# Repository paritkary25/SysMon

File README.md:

# SysMon
SysMon is a system monitor hardware. It has three parts
- USB hub
- macro keys and a volume knob as an input (knobs are cool)
- three strips of multiple colours showing CPU/GPU/RAM usage
The project is ongoing.

.
├── CAD: Contains all the CADs related to the project
├── PCB: Contains the PCB files
├── Software: Software used in this project
└── USB-C_dim_xtracn: An overkill exercise to obtain the correct placement of the holes of the USB-C module

## Progress
- CAD: Complete and printed
- PCB: Complete and printed
    - The USB hub is working
    - STM32 is yet to be tested
- Software: In progress

## Mechanical CAD

The CAD is 3D printed. The enclosure is made slanted to appear like a table clock. The angle is chosen such that it will look good just below the main monitor. The SysMon uses standard Cherry MX keys. Custom keys can be used.

Some of the STEPs are taken from other open-source projects; a sincere thank you to them.

### Log
The CAD has a minor mistake that I noticed after the printing. The inner side of the back body has the wrong angle. Please correct it before printing for yourself. 

## Electronics 
The electronics consist of

- switch matrix
- LED matrix
- volume knob
- Two USB-A upstream ports
- USB-C downstream port for connection to PC
- Adjustable step-down converter module to power the hub
- TI TUSB2036 ASIC-based USB hub 
- STM32L412, very low-powered microcontroller

The PCB is designed on KiCad. For this design, two layers are sufficient. Mixed routing is used with ground planes on both sides. Small series resistors are added in series to the USB-A upstream data bus to prevent ESD issues. Array scanning is used for switches, and row scanning is used for LED lighting.

This hub is not externally powered; take care of what you are plugging in.  The USB-C bus power is set to maximum by pulling CC pins down by 5.1 kOhm (refer to USB-C specifications [USB-C specification](https://www.usb.org/sites/default/files/USB%20Type-C%20Spec%20R2.0%20-%20August%202019_0.pdf) [USB-C PD specifications](https://www.usb.org/sites/default/files/USB-C%20Source%20Power%20Test%20Specification%202021%2005%2024.pdf)))

### Log
- The footprint of the power module is not correct. A workaround involving jumpers and cutting traces is performed.
- The NRST pin of the STM32 is given a test-point only. It is causing discomfort while programming and testing. Please combine it with the SWD programmer pins.

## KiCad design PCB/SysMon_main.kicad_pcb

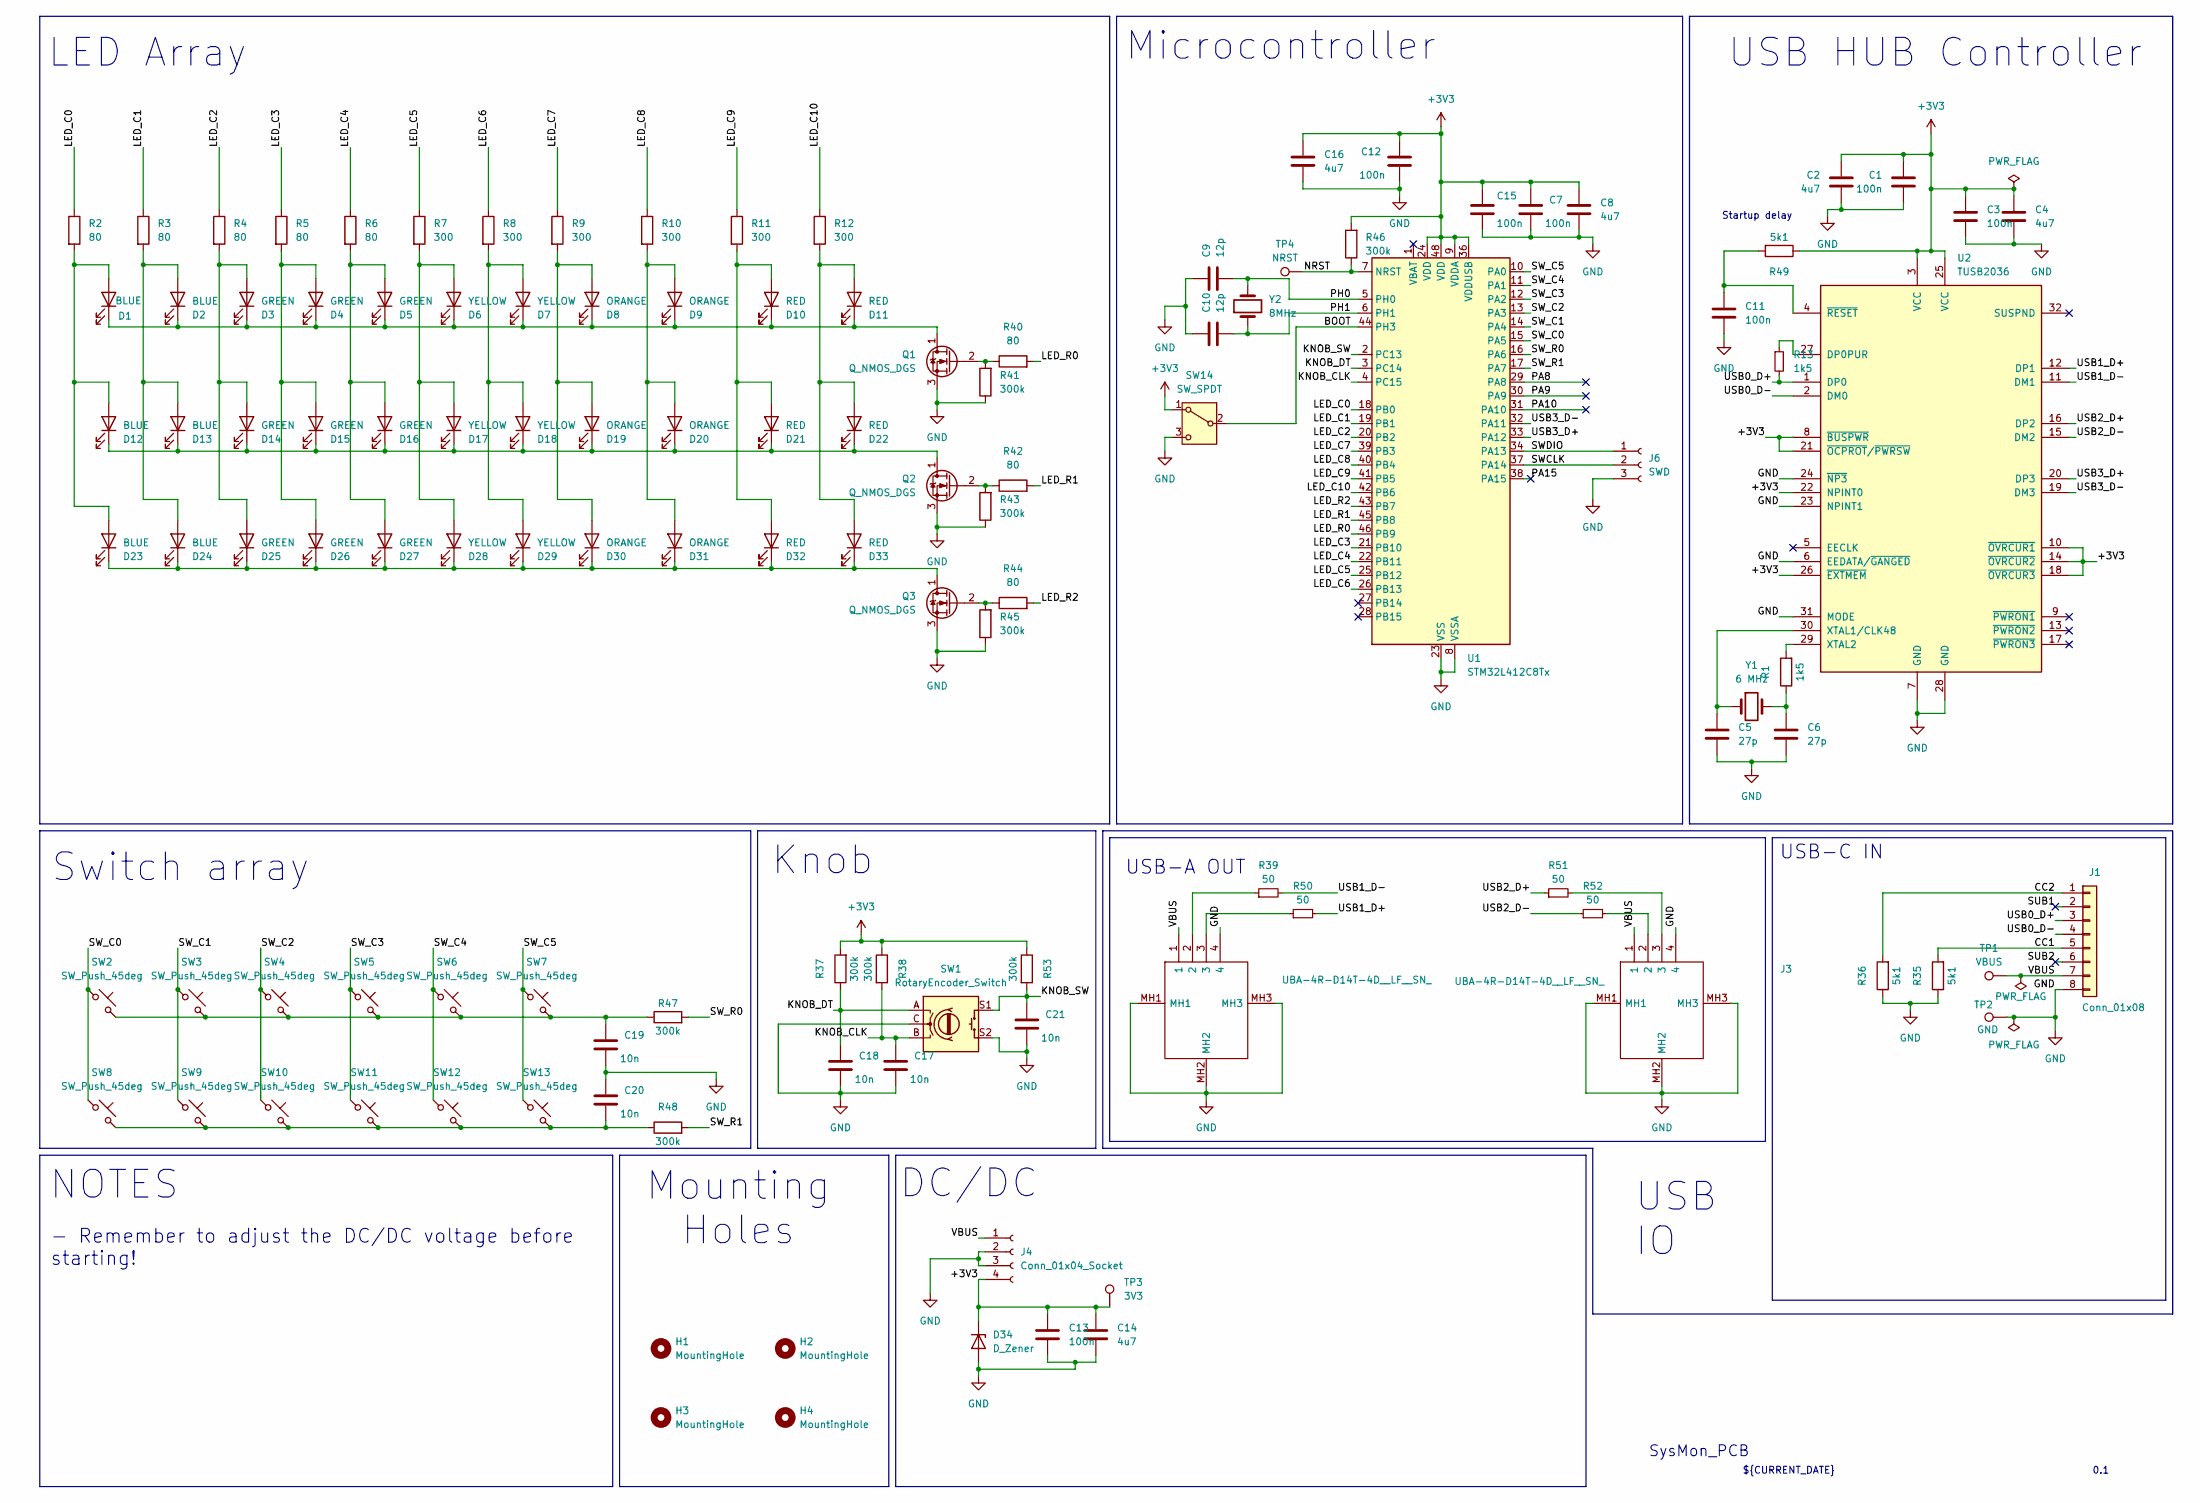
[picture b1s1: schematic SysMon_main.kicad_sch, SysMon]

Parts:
C1, C3, C7, C11, C12, C13, C15: 100n; C_0805_2012Metric
C2, C4, C8, C14, C16: 4u7; C_0805_2012Metric
C5, C6: 27p; C_0805_2012Metric
C9, C10: 12p; C_0805_2012Metric
C17, C18, C19, C20, C21: 10n; C_0805_2012Metric
D1, D2, D12, D13, D23, D24: BLUE; LED_D3.0mm
D3, D4, D5, D14, D15, D16, D25, D26, D27: GREEN; LED_D3.0mm
D6, D7, D17, D18, D28, D29: YELLOW; LED_D3.0mm
D8, D9, D19, D20, D30, D31: ORANGE; LED_D3.0mm
D10, D11, D21, D22, D32, D33: RED; LED_D3.0mm
D34: D_Zener; D_0805_2012Metric
H1, H2, H3, H4: MountingHole; MountingHole_3.2mm_M3
J1: Conn_01x08; USBC_bo
J2, J3: UBA-4R-D14T-4D__LF__SN_; UBA4RD14T4DLFSN; Manufacturer_Part_Number UBA-4R-D14T-4D (LF)(SN)
J4: Conn_01x04_Socket; Mini_360_DCDC
J6: SWD; PinSocket_1x03_P2.54mm_Vertical
Q1, Q2, Q3: Q_NMOS_DGS; SOT-23
R1, R13: 1k5; R_0805_2012Metric
R2, R3, R4, R5, R6, R40, R42, R44: 80; R_0805_2012Metric
R7, R8, R9, R10, R11, R12: 300; R_0805_2012Metric
R35, R36, R49: 5k1; R_0805_2012Metric
R37, R38, R41, R43, R45, R46, R47, R48, R53: 300k; R_0805_2012Metric
R39, R50, R51, R52: 50; R_0603_1608Metric
SW1: RotaryEncoder_Switch; RotaryEncoder_Alps_EC11E-Switch_Vertical_H20mm
SW2, SW3, SW4, SW5, SW6, SW7, SW8, SW9, SW10, SW11, SW12, SW13: SW_Push_45deg; SW_MX_THT
SW14: SW_SPDT; PinHeader_1x03_P2.54mm_Vertical
TP1: VBUS; TestPoint_THTPad_D2.0mm_Drill1.0mm
TP2: GND; TestPoint_THTPad_D2.0mm_Drill1.0mm
TP3: 3V3; TestPoint_THTPad_D2.0mm_Drill1.0mm
TP4: NRST; TestPoint_Pad_D1.0mm
U1: STM32L412C8Tx; LQFP-48_7x7mm_P0.5mm
U2: TUSB2036; LQFP-32_7x7mm_P0.8mm
Y1: 6 MHz; Crystal_HC49-4H_Vertical
Y2: 8MHz; Crystal_HC49-4H_Vertical

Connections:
+3V3: C1.1, C2.1, C3.1, C4.1, C7.1, C8.1, C12.1, C13.1, C14.1, C15.1, C16.1, D34.1 (K), J4.4, R37.2, R38.1, R46.2, R49.1, R53.1, SW14.1 (A), TP3.1, U1.9 (VDDA), U1.24 (VDD), U1.36 (VDDUSB), U1.48 (VDD), U2.3 (VCC), U2.8 (~BUSPWR), U2.10 (~OVRCUR1), U2.14 (~OVRCUR2), U2.18 (~OVRCUR3), U2.21 (~OCPROT/~PWRSW), U2.22 (NPINT0), U2.25 (VCC), U2.26 (~EXTMEM)
/BOOT: SW14.2 (B), U1.44 (PH3)
/CC1: J1.5, R35.2
/CC2: J1.1, R36.2
/KNOB_CLK: C17.1, R38.2, SW1.B, U1.4 (PC15)
/KNOB_DT: C18.1, R37.1, SW1.A, U1.3 (PC14)
/KNOB_SW: C21.1, R53.2, SW1.S1, U1.2 (PC13)
/LED_C0: R2.1, U1.18 (PB0)
/LED_C1: R3.1, U1.19 (PB1)
/LED_C2: R4.1, U1.20 (PB2)
/LED_C3: R5.1, U1.21 (PB10)
/LED_C4: R6.1, U1.22 (PB11)
/LED_C5: R7.1, U1.25 (PB12)
/LED_C6: R8.1, U1.26 (PB13)
/LED_C7: R9.1, U1.39 (PB3)
/LED_C8: R10.1, U1.40 (PB4)
/LED_C9: R11.1, U1.41 (PB5)
/LED_C10: R12.1, U1.42 (PB6)
/LED_R0: R40.2, U1.46 (PB9)
/LED_R1: R42.2, U1.45 (PB8)
/LED_R2: R44.2, U1.43 (PB7)
/NRST: R46.1, TP4.1, U1.7 (NRST)
/PA8: U1.29 (PA8)
/PA9: U1.30 (PA9)
/PA10: U1.31 (PA10)
/PA15: U1.38 (PA15)
/PH0: C9.2, U1.5 (PH0), Y2.2
/PH1: C10.2, U1.6 (PH1), Y2.1
/SUB1: J1.2
/SUB2: J1.6
/SWCLK: J6.2, U1.37 (PA14)
/SWDIO: J6.1, U1.34 (PA13)
/SW_C0: SW2.1, SW8.1, U1.15 (PA5)
/SW_C1: SW3.1, SW9.1, U1.14 (PA4)
/SW_C2: SW4.1, SW10.1, U1.13 (PA3)
/SW_C3: SW5.1, SW11.1, U1.12 (PA2)
/SW_C4: SW6.1, SW12.1, U1.11 (PA1)
/SW_C5: SW7.1, SW13.1, U1.10 (PA0)
/SW_R0: R47.2, U1.16 (PA6)
/SW_R1: R48.2, U1.17 (PA7)
/USB0_D+: J1.3, R13.2, U2.1 (DP0)
/USB0_D-: J1.4, U2.2 (DM0)
/USB1_D+: R50.2, U2.12 (DP1)
/USB1_D-: R39.2, U2.11 (DM1)
/USB2_D+: R51.1, U2.16 (DP2)
/USB2_D-: R52.1, U2.15 (DM2)
/USB3_D+: U1.33 (PA12), U2.20 (DP3)
/USB3_D-: U1.32 (PA11), U2.19 (DM3)
/VBUS: J1.7, J2.1, J3.1, J4.1, TP1.1
GND: C1.2, C2.2, C3.2, C4.2, C5.2, C6.2, C7.2, C8.2, C9.1, C10.1, C11.2, C12.2, C13.2, C14.2, C15.2, C16.2, C17.2, C18.2, C19.2, C20.1, C21.2, D34.2 (A), J1.8, J2.4, J2.MH1, J2.MH2, J2.MH3, J3.4, J3.MH1, J3.MH2, J3.MH3, J4.2, J4.3, J6.3, Q1.3 (S), Q2.3 (S), Q3.3 (S), R35.1, R36.1, R41.1, R43.1, R45.1, SW1.C, SW1.S2, SW14.3 (C), TP2.1, U1.8 (VSSA), U1.23 (VSS), U1.35 (VSS), U1.47 (VSS), U2.6 (EEDATA/~GANGED), U2.7 (GND), U2.23 (NPINT1), U2.24 (~NP3), U2.28 (GND), U2.31 (MODE)
unnamed: C6.1, R1.1, Y1.2
unnamed: C19.1, R47.1, SW2.2, SW3.2, SW4.2, SW5.2, SW6.2, SW7.2
unnamed: C20.2, R48.1, SW8.2, SW9.2, SW10.2, SW11.2, SW12.2, SW13.2
unnamed: D1.2 (A), D12.2 (A), D23.2 (A), R2.2
unnamed: D1.1 (K), D2.1 (K), D3.1 (K), D4.1 (K), D5.1 (K), D6.1 (K), D7.1 (K), D8.1 (K), D9.1 (K), D10.1 (K), D11.1 (K), Q1.1 (D)
unnamed: D10.2 (A), D21.2 (A), D32.2 (A), R11.2
unnamed: D11.2 (A), D22.2 (A), D33.2 (A), R12.2
unnamed: D12.1 (K), D13.1 (K), D14.1 (K), D15.1 (K), D16.1 (K), D17.1 (K), D18.1 (K), D19.1 (K), D20.1 (K), D21.1 (K), D22.1 (K), Q2.1 (D)
unnamed: D2.2 (A), D13.2 (A), D24.2 (A), R3.2
unnamed: D3.2 (A), D14.2 (A), D25.2 (A), R4.2
unnamed: D4.2 (A), D15.2 (A), D26.2 (A), R5.2
unnamed: D5.2 (A), D16.2 (A), D27.2 (A), R6.2
unnamed: D6.2 (A), D17.2 (A), D28.2 (A), R7.2
unnamed: D7.2 (A), D18.2 (A), D29.2 (A), R8.2
unnamed: D8.2 (A), D19.2 (A), D30.2 (A), R9.2
unnamed: D9.2 (A), D20.2 (A), D31.2 (A), R10.2
unnamed: D23.1 (K), D24.1 (K), D25.1 (K), D26.1 (K), D27.1 (K), D28.1 (K), D29.1 (K), D30.1 (K), D31.1 (K), D32.1 (K), D33.1 (K), Q3.1 (D)
unnamed: J2.2, R39.1
unnamed: J2.3, R50.1
unnamed: J3.2, R52.2
unnamed: J3.3, R51.2
unnamed: Q1.2 (G), R40.1, R41.2
unnamed: Q2.2 (G), R42.1, R43.2
unnamed: Q3.2 (G), R44.1, R45.2
unnamed: R13.1, U2.27 (DP0PUR)
unnamed: C5.1, U2.30 (XTAL1/CLK48), Y1.1
unnamed: R1.2, U2.29 (XTAL2)
unnamed: C11.1, R49.2, U2.4 (~RESET)

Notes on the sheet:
0.1
DC/DC
Mounting Holes
USB-A OUT
NOTES
Startup delay
${CURRENT_DATE}
USB-C IN
LED Array
USB IO
Switch array
USB HUB Controller
Knob
Microcontroller
SysMon_PCB
- Remember to adjust the DC/DC voltage before starting!

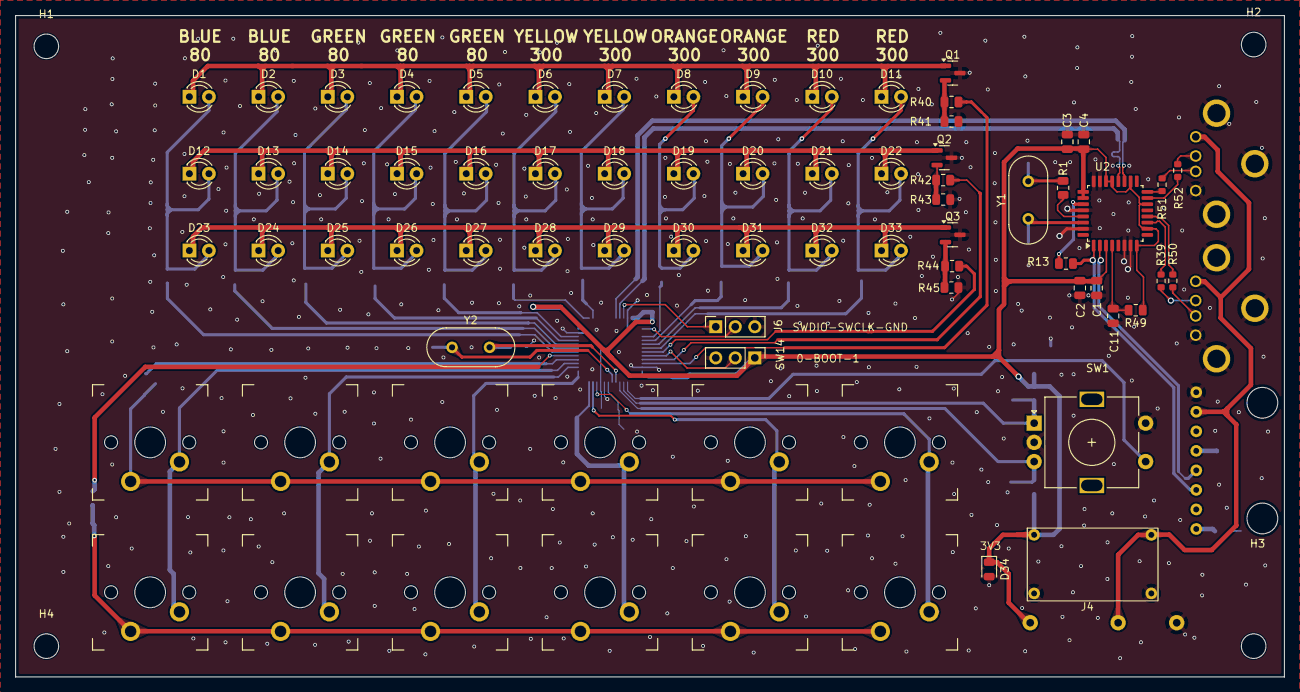
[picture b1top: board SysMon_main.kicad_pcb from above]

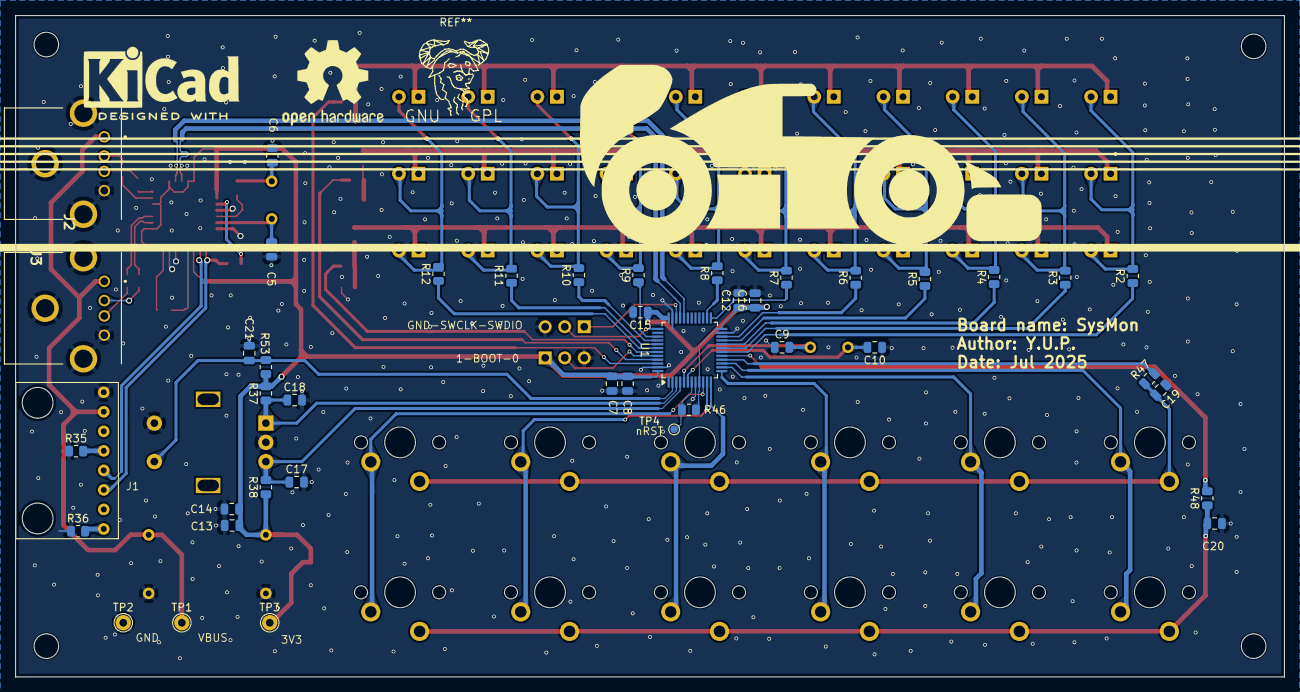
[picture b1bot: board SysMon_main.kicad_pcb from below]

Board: 2 copper layers, 165.0 x 86.0 mm, 121 parts (43 on the bottom side), 72 nets.

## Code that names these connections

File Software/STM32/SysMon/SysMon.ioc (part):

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Mcu.Name=STM32L412CBTx
Mcu.Package=LQFP48
Mcu.UserName=STM32L412CBTx
PA0.Signal=GPIO_Output
PA1.Signal=GPIO_Output
PA11.Mode=Device
PA11.Signal=USB_DM
PA12.Mode=Device
PA12.Signal=USB_DP
PA2.Signal=GPIO_Input
PA3.Signal=GPIO_Analog
PA4.Signal=GPIO_Output
PA5.Signal=GPIO_Output
PA6.Signal=GPIO_Input
PA7.Signal=GPIO_Input
PB0.Signal=GPIO_Output
PB1.Signal=GPIO_Output
PB10.Signal=GPIO_Output
PB11.Signal=GPIO_Output
PB12.Signal=GPIO_Output
PB13.Signal=GPIO_Output
PB2.Signal=GPIO_Output
PB3\ (JTDO/TRACESWO).Signal=GPIO_Output
PB4\ (NJTRST).Signal=GPIO_Output
PB5.Signal=GPIO_Output
PB6.Signal=GPIO_Output
PB7.Signal=GPIO_Output
PB8.Signal=GPIO_Output
PB9.Signal=GPIO_Output
PC13.Signal=GPIO_Input
PC14-OSC32_IN\ (PC14).Signal=GPIO_Input
PC15-OSC32_OUT\ (PC15).Signal=GPIO_Input
PH0-OSC_IN\ (PH0).Mode=HSE-External-Oscillator
PH0-OSC_IN\ (PH0).Signal=RCC_OSC_IN
PH1-OSC_OUT\ (PH1).Mode=HSE-External-Oscillator
PH1-OSC_OUT\ (PH1).Signal=RCC_OSC_OUT
RCC.HSE_VALUE=8000000
RCC.SYSCLKFreq_VALUE=80000000
RCC.SYSCLKSource=RCC_SYSCLKSOURCE_PLLCLK
board=custom

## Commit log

2026-01-02 removed unnecessary build files
2026-01-03 improve readme
